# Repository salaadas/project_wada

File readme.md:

# Project Wada

Although I love my HHKB Pro 2, sometimes I just want some arrow keys for gaming. This made me learn how to design a PCB and make it has a layout somewhat similar to the HHKB. I also realized that the Realforce RC1 kinda has the same layout as this keyboard too.

Anyways, here is the layout.

## Incomplete..... more to come after I finished!

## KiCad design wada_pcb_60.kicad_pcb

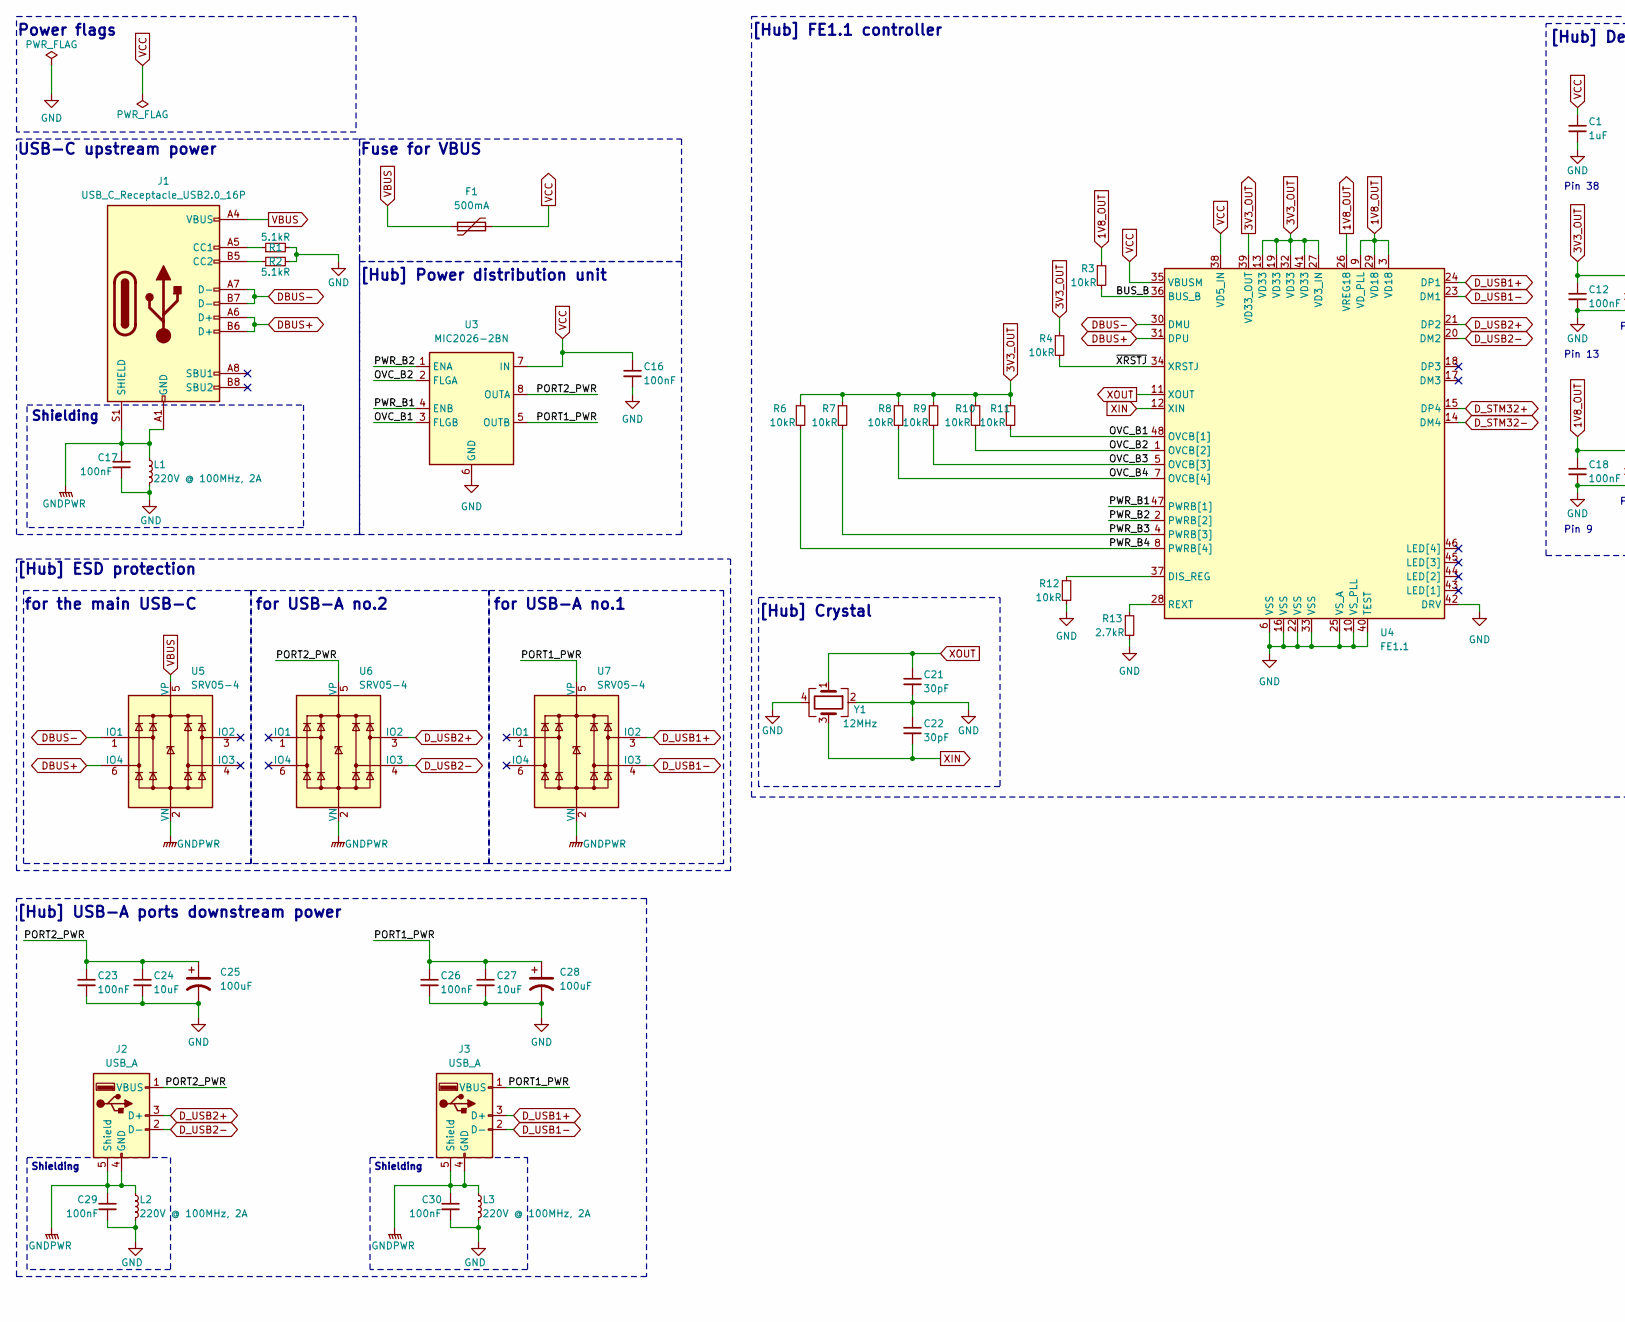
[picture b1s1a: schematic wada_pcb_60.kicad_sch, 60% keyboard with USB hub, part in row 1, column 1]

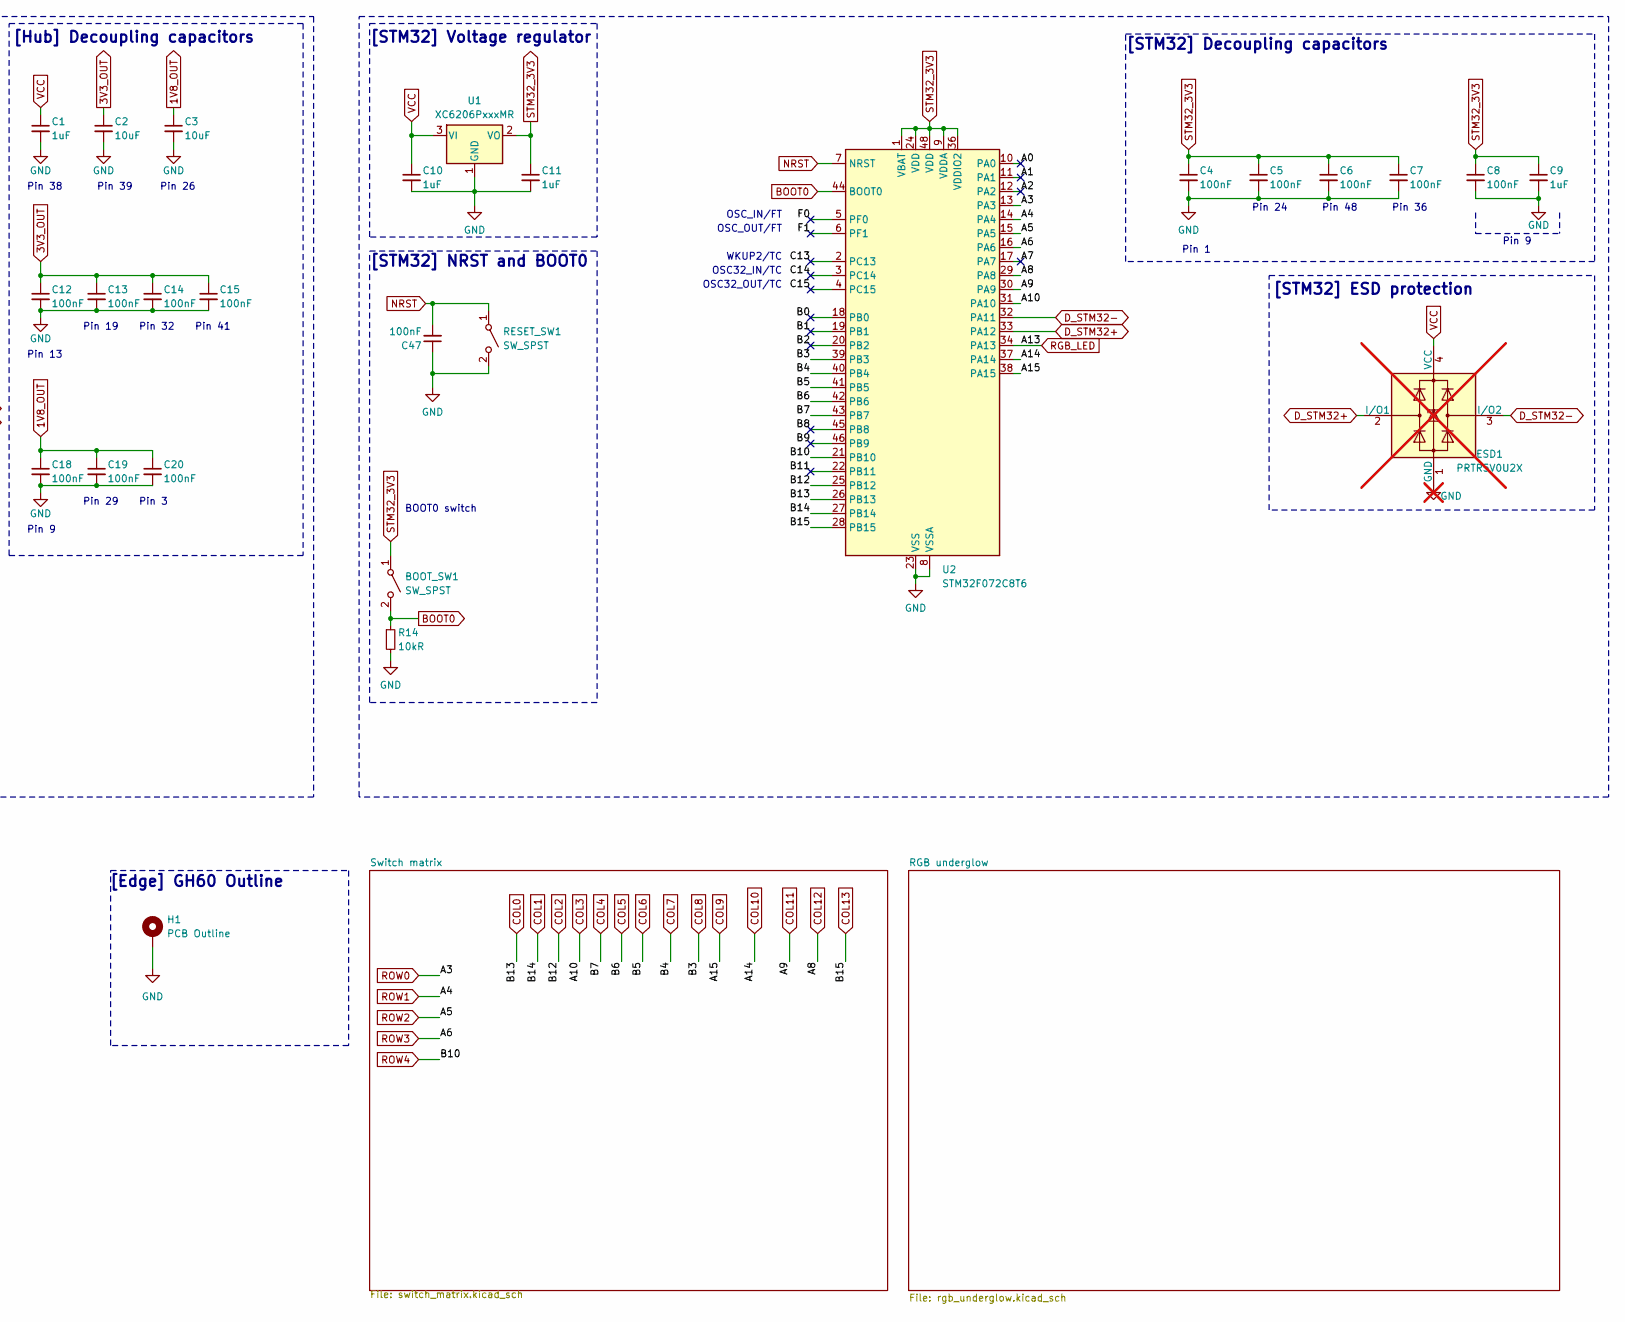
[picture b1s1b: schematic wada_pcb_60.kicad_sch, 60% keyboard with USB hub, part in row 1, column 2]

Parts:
BOOT_SW1: SW_SPST; SW_SPST_TL3342
C1, C9, C10, C11: 1uF; C_0603_1608Metric
C2, C3, C24, C27: 10uF; C_0603_1608Metric
C4, C5, C6, C7, C8, C12, C13, C14, C15, C16, C17, C18, C19, C20, C23, C26, C29, C30, C47: 100nF; C_0603_1608Metric
C21, C22: 30pF; C_0603_1608Metric
C25, C28: 100uF; CP_Elec_6.3x5.9
ESD1: PRTR5V0U2X; SOT-143; not fitted
F1: 500mA; Fuse_1206_3216Metric
H1: PCB Outline; GH60_outline_without_bottom_mounting
J1: USB_C_Receptacle_USB2.0_16P; USB_C_Receptacle_HRO_TYPE-C-31-M-12
J2, J3: USB_A; JING 903-231A2031S10100
L1, L2, L3: 220V @ 100MHz, 2A; L_0603_1608Metric
R1, R2: 5.1kR; R_0402_1005Metric
R3, R4, R6, R7, R8, R9, R10, R11, R12, R14: 10kR; R_0603_1608Metric
R13: 2.7kR; R_0603_1608Metric
RESET_SW1: SW_SPST; SW_SPST_TL3342
U1: XC6206PxxxMR; SOT-23
U2: STM32F072C8T6; LQFP-48_7x7mm_P0.5mm
U3: MIC2026-2BN; SOIC-8_3.9x4.9mm_P1.27mm
U4: FE1.1; LQFP-48_7x7mm_P0.5mm
U5, U6, U7: SRV05-4; SOT-23-6-routable
Y1: 12MHz; Crystal_SMD_3225-4pin_3.2x2.5mm

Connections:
1V8_OUT: C3.1, C18.1, C19.1, C20.1, R3.1, U4.3 (VD18), U4.9 (VD_PLL), U4.26 (VREG18), U4.29 (VD18)
3V3_OUT: C2.1, C12.1, C13.1, C14.1, C15.1, R4.1, R6.1, R7.1, R8.1, R9.1, R10.1, R11.1, U4.13 (VD33), U4.19 (VD33), U4.27 (VD3_IN), U4.32 (VD33), U4.39 (VD33_OUT), U4.41 (VD33)
/A0: U2.10 (PA0)
/A1: U2.11 (PA1)
/A2: U2.12 (PA2)
/A7: U2.17 (PA7)
/B0: U2.18 (PB0)
/B1: U2.19 (PB1)
/B2: U2.20 (PB2)
/B8: U2.45 (PB8)
/B9: U2.46 (PB9)
/B11: U2.22 (PB11)
/BUS_B: R3.2, U4.36 (BUS_B)
/C13: U2.2 (PC13)
/C14: U2.3 (PC14)
/C15: U2.4 (PC15)
/F0: U2.5 (PF0)
/F1: U2.6 (PF1)
/OVC_B1: R11.2, U3.3 (FLGB), U4.48 (OVCB[1])
/OVC_B2: R10.2, U3.2 (FLGA), U4.1 (OVCB[2])
/OVC_B3: R9.2, U4.5 (OVCB[3])
/OVC_B4: R8.2, U4.7 (OVCB[4])
/PORT1_PWR: C26.1, C27.1, C28.1, J3.1 (VBUS), U3.5 (OUTB), U7.5 (VP)
/PORT2_PWR: C23.1, C24.1, C25.1, J2.1 (VBUS), U3.8 (OUTA), U6.5 (VP)
/PWR_B1: U3.4 (ENB), U4.47 (PWRB[1])
/PWR_B2: U3.1 (ENA), U4.2 (PWRB[2])
/PWR_B3: R7.2, U4.4 (PWRB[3])
/PWR_B4: R6.2, U4.8 (PWRB[4])
/~XRSTJ: R4.2, U4.34 (XRSTJ)
BOOT0: BOOT_SW1.2 (B), R14.1, U2.44 (BOOT0)
COL0: U2.26 (PB13); also elsewhere on the board
COL1: U2.27 (PB14); also elsewhere on the board
COL2: U2.25 (PB12); also elsewhere on the board
COL3: U2.31 (PA10); also elsewhere on the board
COL4: U2.43 (PB7); also elsewhere on the board
COL5: U2.42 (PB6); also elsewhere on the board
COL6: U2.41 (PB5); also elsewhere on the board
COL7: U2.40 (PB4); also elsewhere on the board
COL8: U2.39 (PB3); also elsewhere on the board
COL9: U2.38 (PA15); also elsewhere on the board
COL10: U2.37 (PA14); also elsewhere on the board
COL11: U2.30 (PA9); also elsewhere on the board
COL12: U2.29 (PA8); also elsewhere on the board
COL13: U2.28 (PB15); also elsewhere on the board
DBUS+: J1.A6 (D+), J1.B6 (D+), U4.31 (DPU), U5.6 (IO4)
DBUS-: J1.A7 (D-), J1.B7 (D-), U4.30 (DMU), U5.1 (IO1)
D_STM32+: ESD1.2 (I/O1), U2.33 (PA12), U4.15 (DP4)
D_STM32-: ESD1.3 (I/O2), U2.32 (PA11), U4.14 (DM4)
D_USB1+: J3.3 (D+), U4.24 (DP1), U7.3 (IO2)
D_USB1-: J3.2 (D-), U4.23 (DM1), U7.4 (IO3)
D_USB2+: J2.3 (D+), U4.21 (DP2), U6.3 (IO2)
D_USB2-: J2.2 (D-), U4.20 (DM2), U6.4 (IO3)
GND: C1.2, C2.2, C3.2, C4.2, C5.2, C6.2, C7.2, C8.2, C9.2, C10.2, C11.2, C12.2, C13.2, C14.2, C15.2, C16.2, C17.2, C18.2, C19.2, C20.2, C21.2, C22.1, C23.2, C24.2, C25.2, C26.2, C27.2, C28.2, C29.2, C30.2, C47.1, ESD1.1 (GND), H1.1, L1.2, L2.2, L3.2, R1.2, R2.2, R12.2, R13.2, R14.2, RESET_SW1.2 (B), U1.1 (GND), U2.8 (VSSA), U2.23 (VSS), U2.35 (VSS), U2.47 (VSS), U3.6 (GND), U4.6 (VSS), U4.10 (VS_PLL), U4.16 (VSS), U4.22 (VSS), U4.25 (VS_A), U4.33 (VSS), U4.40 (TEST), U4.42 (DRV), Y1.2, Y1.4; also elsewhere on the board
GNDPWR: C17.1, C29.1, C30.1, J1.A1 (GND), J1.A12 (GND), J1.B1 (GND), J1.B12 (GND), J1.S1 (SHIELD), J2.4 (GND), J2.5 (Shield), J3.4 (GND), J3.5 (Shield), L1.1, L2.1, L3.1, U5.2 (VN), U6.2 (VN), U7.2 (VN)
NRST: C47.2, RESET_SW1.1 (A), U2.7 (NRST)
unnamed: J1.A5 (CC1), R1.1
unnamed: J1.B5 (CC2), R2.1
unnamed: R12.1, U4.37 (DIS_REG)
unnamed: R13.1, U4.28 (REXT)
RGB_LED: U2.34 (PA13); also elsewhere on the board
ROW0: U2.13 (PA3); also elsewhere on the board
ROW1: U2.14 (PA4); also elsewhere on the board
ROW2: U2.15 (PA5); also elsewhere on the board
ROW3: U2.16 (PA6); also elsewhere on the board
ROW4: U2.21 (PB10); also elsewhere on the board
STM32_3V3: BOOT_SW1.1 (A), C4.1, C5.1, C6.1, C7.1, C8.1, C9.1, C11.1, U1.2 (VO), U2.1 (VBAT), U2.9 (VDDA), U2.24 (VDD), U2.36 (VDDIO2), U2.48 (VDD)
VBUS: F1.1, J1.A4 (VBUS), J1.A9 (VBUS), J1.B4 (VBUS), J1.B9 (VBUS), U5.5 (VP)
VCC: C1.1, C10.1, C16.1, ESD1.4 (VCC), F1.2, U1.3 (VI), U3.7 (IN), U4.35 (VBUSM), U4.38 (VD5_IN); also elsewhere on the board
XIN: C22.2, U4.12 (XIN), Y1.3
XOUT: C21.1, U4.11 (XOUT), Y1.1

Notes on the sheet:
for USB-A no.1
Shielding
[Hub] ESD protection
Pin 24
Pin 32
Pin 9
USB-C upstream power
OSC_OUT/FT
OSC32_OUT/TC
Pin 29
Pin 26
OSC32_IN/TC
Pin 3
Pin 38
[Hub] USB-A ports downstream power
OSC_IN/FT
[Edge] GH60 Outline
[STM32] ESD protection
Fuse for VBUS
[Hub] Decoupling capacitors
WKUP2/TC
Pin 36
Pin 39
Pin 48
[STM32] Voltage regulator
Pin 19
Pin 41
for USB-A no.2
Power flags
[Hub] Power distribution unit
Pin 1
for the main USB-C
[STM32] Decoupling capacitors
[STM32] NRST and BOOT0
[Hub] FE1.1 controller
[Hub] Crystal
Pin 13
BOOT0 switch

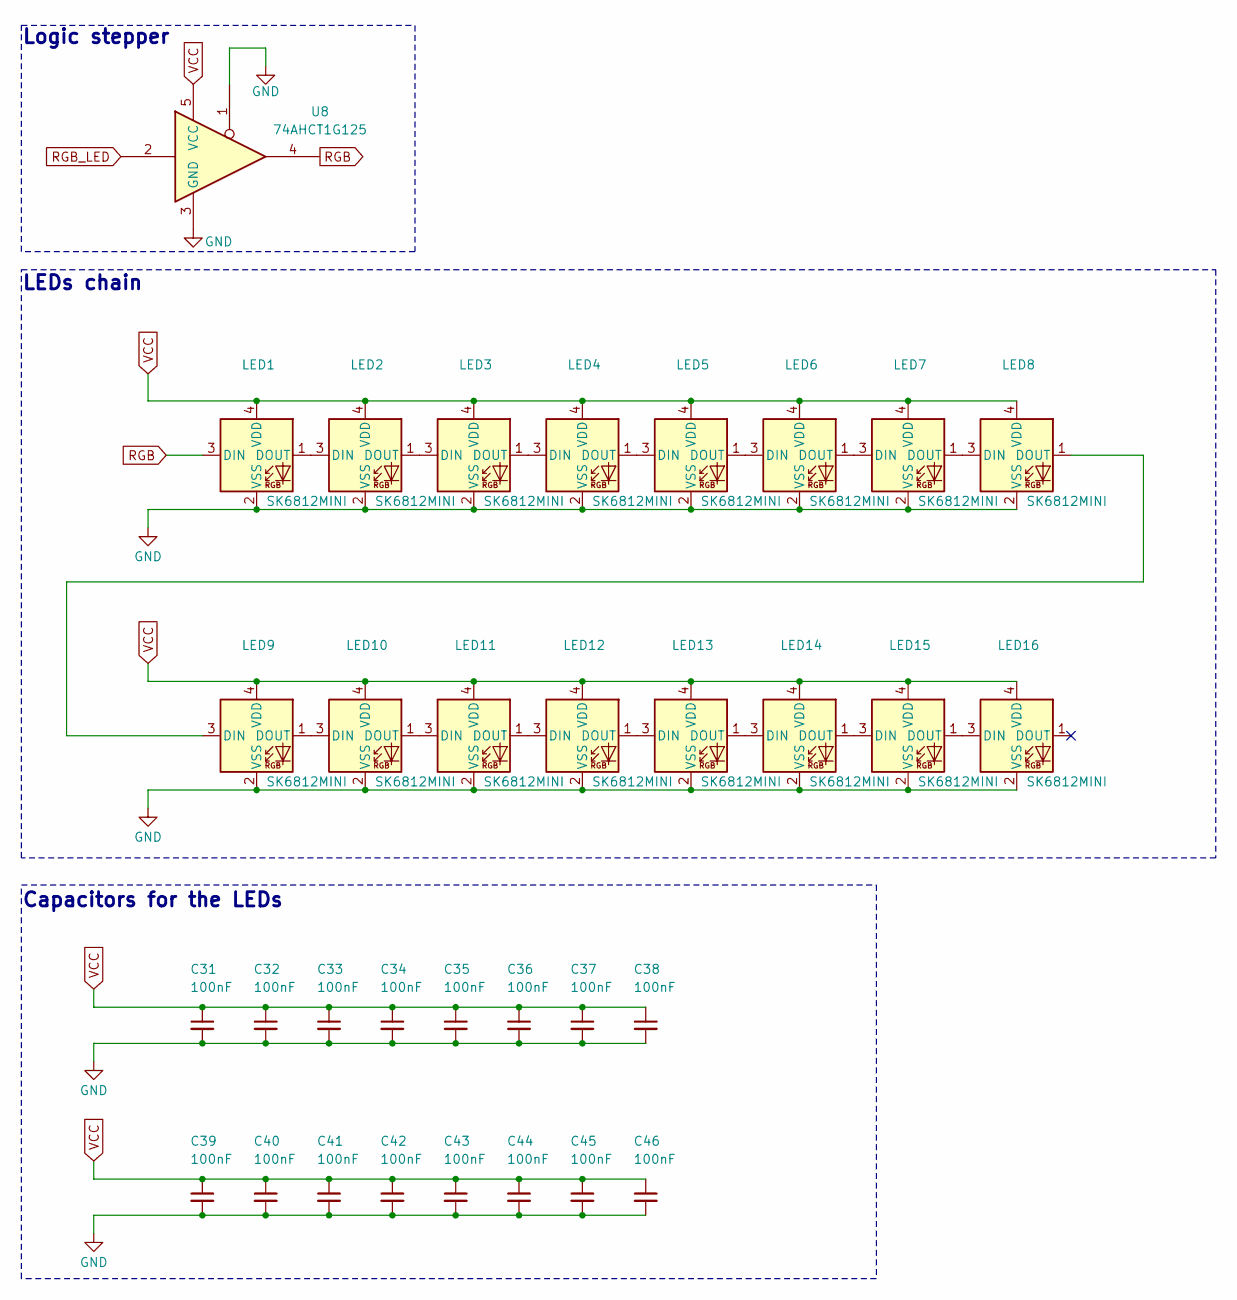
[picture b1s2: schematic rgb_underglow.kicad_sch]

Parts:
C31, C32, C33, C34, C35, C36, C37, C38, C39, C40, C41, C42, C43, C44, C45, C46: 100nF; C_0603_1608Metric
LED1, LED2, LED3, LED4, LED5, LED6, LED7, LED8, LED9, LED10, LED11, LED12, LED13, LED14, LED15, LED16: SK6812MINI; LED_SK6812MINI_HAND_SOLDER_3.5x3.5mm_P1.75mm
U8: 74AHCT1G125; SOT-23-5

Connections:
GND: C31.2, C32.2, C33.2, C34.2, C35.2, C36.2, C37.2, C38.2, C39.2, C40.2, C41.2, C42.2, C43.2, C44.2, C45.2, C46.2, LED1.2 (VSS), LED2.2 (VSS), LED3.2 (VSS), LED4.2 (VSS), LED5.2 (VSS), LED6.2 (VSS), LED7.2 (VSS), LED8.2 (VSS), LED9.2 (VSS), LED10.2 (VSS), LED11.2 (VSS), LED12.2 (VSS), LED13.2 (VSS), LED14.2 (VSS), LED15.2 (VSS), LED16.2 (VSS), U8.1, U8.3 (GND); also elsewhere on the board
unnamed: LED1.1 (DOUT), LED2.3 (DIN)
unnamed: LED2.1 (DOUT), LED3.3 (DIN)
unnamed: LED3.1 (DOUT), LED4.3 (DIN)
unnamed: LED4.1 (DOUT), LED5.3 (DIN)
unnamed: LED5.1 (DOUT), LED6.3 (DIN)
unnamed: LED6.1 (DOUT), LED7.3 (DIN)
unnamed: LED7.1 (DOUT), LED8.3 (DIN)
unnamed: LED8.1 (DOUT), LED9.3 (DIN)
unnamed: LED9.1 (DOUT), LED10.3 (DIN)
unnamed: LED10.1 (DOUT), LED11.3 (DIN)
unnamed: LED11.1 (DOUT), LED12.3 (DIN)
unnamed: LED12.1 (DOUT), LED13.3 (DIN)
unnamed: LED13.1 (DOUT), LED14.3 (DIN)
unnamed: LED14.1 (DOUT), LED15.3 (DIN)
unnamed: LED15.1 (DOUT), LED16.3 (DIN)
RGB: LED1.3 (DIN), U8.4
RGB_LED: U8.2; also elsewhere on the board
VCC: C31.1, C32.1, C33.1, C34.1, C35.1, C36.1, C37.1, C38.1, C39.1, C40.1, C41.1, C42.1, C43.1, C44.1, C45.1, C46.1, LED1.4 (VDD), LED2.4 (VDD), LED3.4 (VDD), LED4.4 (VDD), LED5.4 (VDD), LED6.4 (VDD), LED7.4 (VDD), LED8.4 (VDD), LED9.4 (VDD), LED10.4 (VDD), LED11.4 (VDD), LED12.4 (VDD), LED13.4 (VDD), LED14.4 (VDD), LED15.4 (VDD), LED16.4 (VDD), U8.5 (VCC); also elsewhere on the board

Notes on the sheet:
LEDs chain
Logic stepper
Capacitors for the LEDs

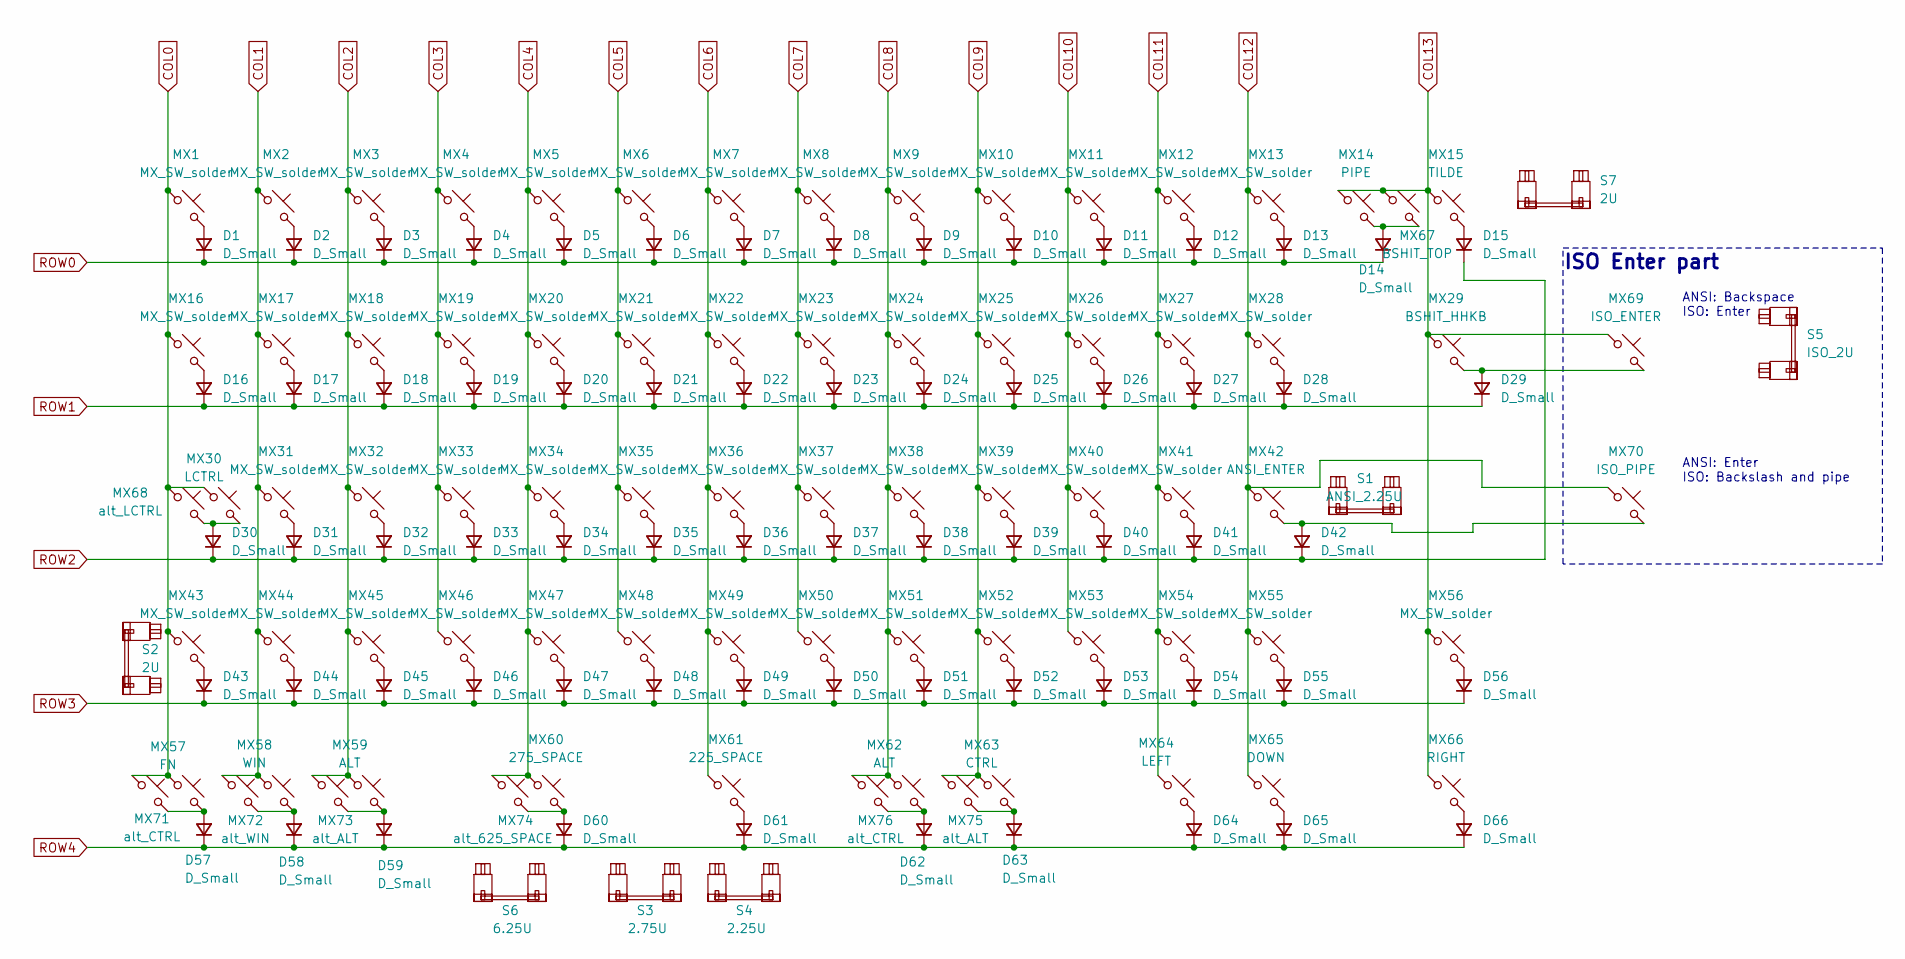
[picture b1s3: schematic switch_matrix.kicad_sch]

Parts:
D1, D2, D3, D4, D5, D6, D7, D8, D9, D10, D11, D12, D13, D14, D15, D16, D17, D18, D19, D20, D21, D22, D23, D24, D25, D26, D27, D28, D29, D30, D31, D32, D33, D34, D35, D36, D37, D38, D39, D40, D41, D42, D43, D44, D45, D46, D47, D48, D49, D50, D51, D52, D53, D54, D55, D56, D57, D58, D59, D60, D61, D62, D63, D64, D65, D66: D_Small; D_SOD-123
MX1, MX2, MX3, MX4, MX5, MX6, MX7, MX8, MX9, MX10, MX11, MX12, MX13, MX17, MX18, MX19, MX20, MX21, MX22, MX23, MX24, MX25, MX26, MX27, MX28, MX31, MX32, MX33, MX34, MX35, MX36, MX37, MX38, MX39, MX40, MX41, MX43, MX44, MX45, MX46, MX47, MX48, MX49, MX50, MX51, MX52, MX53, MX54, MX55, MX56: MX_SW_solder; SW_MX_1u
MX14: PIPE; SW_MX_1u
MX15: TILDE; SW_MX_1u
MX16: MX_SW_solder; SW_MX_1.5u
MX29: BSHIT_HHKB; SW_MX_1.5u
MX30: LCTRL; SW_MX_1.75u
MX42: ANSI_ENTER; SW_MX_1u
MX57: FN; SW_MX_1u
MX58: WIN; SW_MX_1.25u
MX59, MX62: ALT; SW_MX_1.5u
MX60: 275_SPACE; SW_MX_1u
MX61: 225_SPACE; SW_MX_1u
MX63: CTRL; SW_MX_1.25u
MX64: LEFT; SW_MX_1u
MX65: DOWN; SW_MX_1u
MX66: RIGHT; SW_MX_1u
MX67: BSHIT_TOP; SW_MX_1u
MX68: alt_LCTRL; SW_MX_1.75u_STP_1.25
MX69: ISO_ENTER; SW_MX_1u
MX70: ISO_PIPE; SW_MX_1u
MX71: alt_CTRL; SW_MX_1.25u
MX72: alt_WIN; SW_MX_1u
MX73, MX75: alt_ALT; SW_MX_1.25u
MX74: alt_625_SPACE; SW_MX_1u
MX76: alt_CTRL; SW_MX_1u
S1: ANSI_2.25U; STAB_MX_2.25u
S2: 2U; STAB_MX_P_2u
S3: 2.75U; STAB_MX_P_2.75u
S4: 2.25U; STAB_MX_P_2.25u
S5: ISO_2U; STAB_MX_ISO-ROT
S6: 6.25U; STAB_MX_P_6.25u
S7: 2U; STAB_MX_2u

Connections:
COL0: MX1.1, MX16.1, MX30.1, MX43.1, MX57.1, MX68.1, MX71.1; also elsewhere on the board
COL1: MX2.1, MX17.1, MX31.1, MX44.1, MX58.1, MX72.1; also elsewhere on the board
COL2: MX3.1, MX18.1, MX32.1, MX45.1, MX59.1, MX73.1; also elsewhere on the board
COL3: MX4.1, MX19.1, MX33.1, MX46.1; also elsewhere on the board
COL4: MX5.1, MX20.1, MX34.1, MX47.1, MX60.1, MX74.1; also elsewhere on the board
COL5: MX6.1, MX21.1, MX35.1, MX48.1; also elsewhere on the board
COL6: MX7.1, MX22.1, MX36.1, MX49.1, MX61.1; also elsewhere on the board
COL7: MX8.1, MX23.1, MX37.1, MX50.1; also elsewhere on the board
COL8: MX9.1, MX24.1, MX38.1, MX51.1, MX62.1, MX76.1; also elsewhere on the board
COL9: MX10.1, MX25.1, MX39.1, MX52.1, MX63.1, MX75.1; also elsewhere on the board
COL10: MX11.1, MX26.1, MX40.1, MX53.1; also elsewhere on the board
COL11: MX12.1, MX27.1, MX41.1, MX54.1, MX64.1; also elsewhere on the board
COL12: MX13.1, MX28.1, MX42.1, MX55.1, MX65.1, MX70.1; also elsewhere on the board
COL13: MX14.1, MX15.1, MX29.1, MX56.1, MX66.1, MX67.1, MX69.1; also elsewhere on the board
unnamed: D1.2 (A), MX1.2
unnamed: D2.2 (A), MX2.2
unnamed: D3.2 (A), MX3.2
unnamed: D4.2 (A), MX4.2
unnamed: D5.2 (A), MX5.2
unnamed: D6.2 (A), MX6.2
unnamed: D7.2 (A), MX7.2
unnamed: D8.2 (A), MX8.2
unnamed: D9.2 (A), MX9.2
unnamed: D10.2 (A), MX10.2
unnamed: D11.2 (A), MX11.2
unnamed: D12.2 (A), MX12.2
unnamed: D13.2 (A), MX13.2
unnamed: D14.2 (A), MX14.2, MX67.2
unnamed: D15.2 (A), MX15.2
unnamed: D16.2 (A), MX16.2
unnamed: D17.2 (A), MX17.2
unnamed: D18.2 (A), MX18.2
unnamed: D19.2 (A), MX19.2
unnamed: D20.2 (A), MX20.2
unnamed: D21.2 (A), MX21.2
unnamed: D22.2 (A), MX22.2
unnamed: D23.2 (A), MX23.2
unnamed: D24.2 (A), MX24.2
unnamed: D25.2 (A), MX25.2
unnamed: D26.2 (A), MX26.2
unnamed: D27.2 (A), MX27.2
unnamed: D28.2 (A), MX28.2
unnamed: D29.2 (A), MX29.2, MX69.2
unnamed: D30.2 (A), MX30.2, MX68.2
unnamed: D31.2 (A), MX31.2
unnamed: D32.2 (A), MX32.2
unnamed: D33.2 (A), MX33.2
unnamed: D34.2 (A), MX34.2
unnamed: D35.2 (A), MX35.2
unnamed: D36.2 (A), MX36.2
unnamed: D37.2 (A), MX37.2
unnamed: D38.2 (A), MX38.2
unnamed: D39.2 (A), MX39.2
unnamed: D40.2 (A), MX40.2
unnamed: D41.2 (A), MX41.2
unnamed: D42.2 (A), MX42.2, MX70.2
unnamed: D43.2 (A), MX43.2
unnamed: D44.2 (A), MX44.2
unnamed: D45.2 (A), MX45.2
unnamed: D46.2 (A), MX46.2
unnamed: D47.2 (A), MX47.2
unnamed: D48.2 (A), MX48.2
unnamed: D49.2 (A), MX49.2
unnamed: D50.2 (A), MX50.2
unnamed: D51.2 (A), MX51.2
unnamed: D52.2 (A), MX52.2
unnamed: D53.2 (A), MX53.2
unnamed: D54.2 (A), MX54.2
unnamed: D55.2 (A), MX55.2
unnamed: D56.2 (A), MX56.2
unnamed: D57.2 (A), MX57.2, MX71.2
unnamed: D58.2 (A), MX58.2, MX72.2
unnamed: D59.2 (A), MX59.2, MX73.2
unnamed: D60.2 (A), MX60.2, MX74.2
unnamed: D61.2 (A), MX61.2
unnamed: D62.2 (A), MX62.2, MX76.2
unnamed: D63.2 (A), MX63.2, MX75.2
unnamed: D64.2 (A), MX64.2
unnamed: D65.2 (A), MX65.2
unnamed: D66.2 (A), MX66.2
ROW0: D1.1 (K), D2.1 (K), D3.1 (K), D4.1 (K), D5.1 (K), D6.1 (K), D7.1 (K), D8.1 (K), D9.1 (K), D10.1 (K), D11.1 (K), D12.1 (K), D13.1 (K), D14.1 (K); also elsewhere on the board
ROW1: D16.1 (K), D17.1 (K), D18.1 (K), D19.1 (K), D20.1 (K), D21.1 (K), D22.1 (K), D23.1 (K), D24.1 (K), D25.1 (K), D26.1 (K), D27.1 (K), D28.1 (K), D29.1 (K); also elsewhere on the board
ROW2: D15.1 (K), D30.1 (K), D31.1 (K), D32.1 (K), D33.1 (K), D34.1 (K), D35.1 (K), D36.1 (K), D37.1 (K), D38.1 (K), D39.1 (K), D40.1 (K), D41.1 (K), D42.1 (K); also elsewhere on the board
ROW3: D43.1 (K), D44.1 (K), D45.1 (K), D46.1 (K), D47.1 (K), D48.1 (K), D49.1 (K), D50.1 (K), D51.1 (K), D52.1 (K), D53.1 (K), D54.1 (K), D55.1 (K), D56.1 (K); also elsewhere on the board
ROW4: D57.1 (K), D58.1 (K), D59.1 (K), D60.1 (K), D61.1 (K), D62.1 (K), D63.1 (K), D64.1 (K), D65.1 (K), D66.1 (K); also elsewhere on the board

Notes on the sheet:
ANSI: Backspace ISO: Enter
ISO Enter part
ANSI: Enter ISO: Backslash and pipe

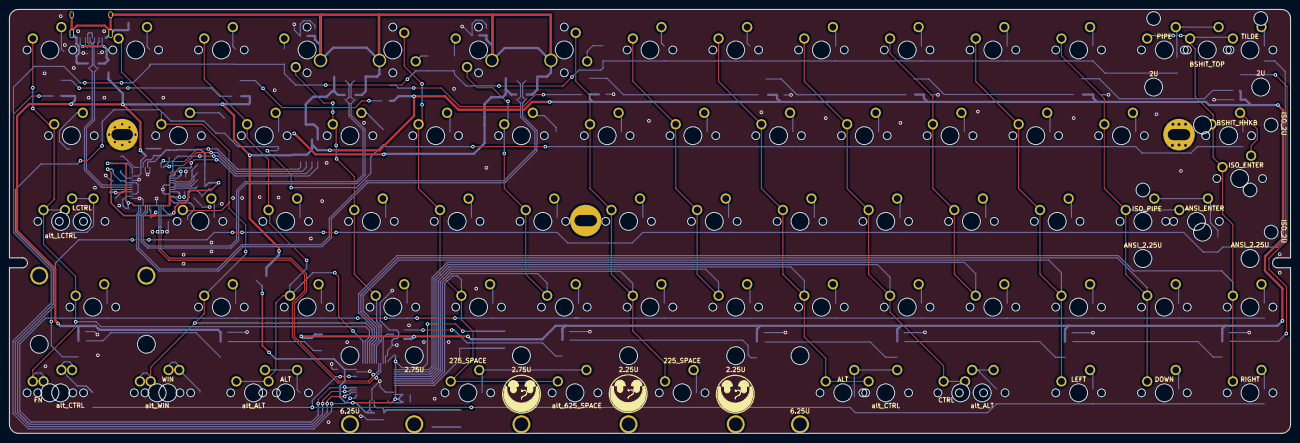
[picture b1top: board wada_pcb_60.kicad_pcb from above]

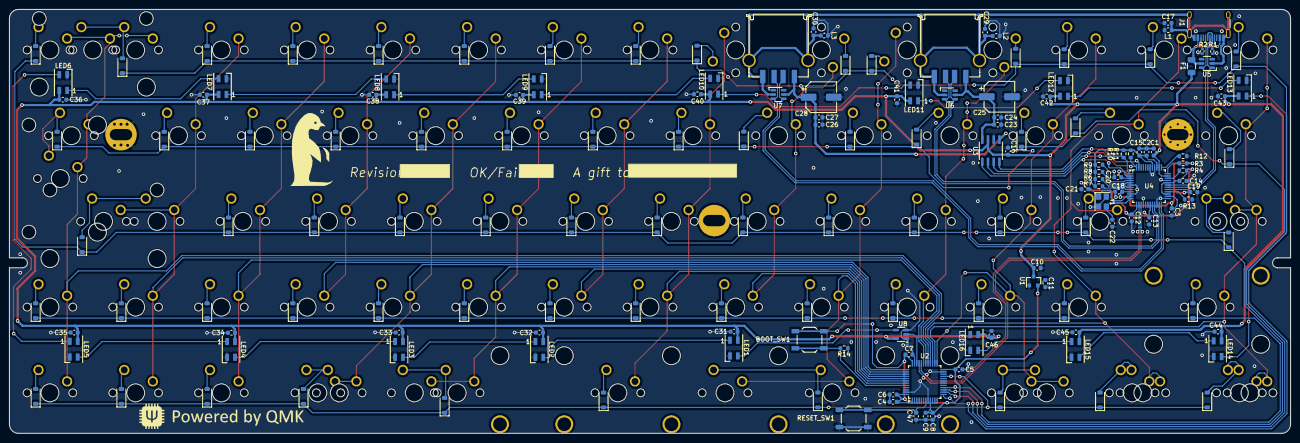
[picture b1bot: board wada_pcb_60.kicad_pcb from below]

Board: 2 copper layers, 284.7 x 94.2 mm, 244 parts (160 on the bottom side), 137 nets.

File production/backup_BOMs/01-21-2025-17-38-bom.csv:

Designator,Footprint,Quantity,Value,LCSC Part #
"BOOT_SW1, RESET_SW1",SW_SPST_TL3342,2,SW_SPST,C318884
"C1, C10, C11, C9",603,4,1uF,C15849
"C12, C13, C14, C15, C16, C17, C18, C19, C20, C23, C26, C29, C30, C31, C32, C33, C34, C35, C36, C37, C38, C39, C4, C40, C41, C42, C43, C44, C45, C46, C47, C5, C6, C7, C8",603,35,100nF,C14663
"C2, C24, C27, C3",603,4,10uF,C19702
"C21, C22",603,2,30pF,C1658
"C25, C28",CP_Elec_6.3x5.9,2,100uF,C134878
"D1, D10, D11, D12, D13, D14, D15, D16, D17, D18, D19, D2, D20, D21, D22, D23, D24, D25, D26, D27, D28, D29, D3, D30, D31, D32, D33, D34, D35, D36, D37, D38, D39, D4, D40, D41, D42, D43, D44, D45, D46, D47, D48, D49, D5, D50, D51, D52, D53, D54, D55, D56, D57, D58, D59, D6, D60, D61, D62, D63, D64, D65, D66, D7, D8, D9",D_SOD-123,66,D_Small,C81598
F1,1206,1,500mA,C70076
J1,USB_C_Receptacle_HRO_TYPE-C-31-M-12,1,USB_C_Receptacle_USB2.0_16P,C165948
"J2, J3",JING 903-231A2031S10100,2,USB_A,C42646
"L1, L2, L3",603,3,"220V @ 100MHz, 2A",C85832
"LED1, LED10, LED11, LED12, LED13, LED14, LED15, LED16, LED2, LED3, LED4, LED5, LED6, LED7, LED8, LED9",LED_SK6812MINI_HAND_SOLDER_3.5x3.5mm_P1.75mm,16,SK6812MINI,C2922787
"R1, R2",402,2,5.1kR,C25905
"R10, R11, R12, R14, R3, R4, R6, R7, R8, R9",603,10,10kR,C25804
R13,603,1,2.7kR,C13167
U1,SOT-23,1,XC6206PxxxMR,C5446
U2,LQFP-48_7x7mm_P0.5mm,1,STM32F072C8T6,C81720
U3,SOIC-8_3.9x4.9mm_P1.27mm,1,MIC2026-2BN,C148072
U4,LQFP-48_7x7mm_P0.5mm,1,FE1.1,C28958
"U5, U6, U7",SOT-23-6-routable,3,SRV05-4,C85364
U8,SOT-23-5,1,74AHCT1G125,C7484
Y1,Crystal_SMD_3225-4pin_3.2x2.5mm,1,12MHz,C9002

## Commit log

2025-01-18 subversion to fucking git
2025-01-18 hey!
2025-01-19 wired up the LEDS, rows, and columns!
2025-01-20 done! missing the reset switch!
2025-01-20 review time!
2025-01-21 Changed USB type-A and LED parts
2025-01-21 checking phase
